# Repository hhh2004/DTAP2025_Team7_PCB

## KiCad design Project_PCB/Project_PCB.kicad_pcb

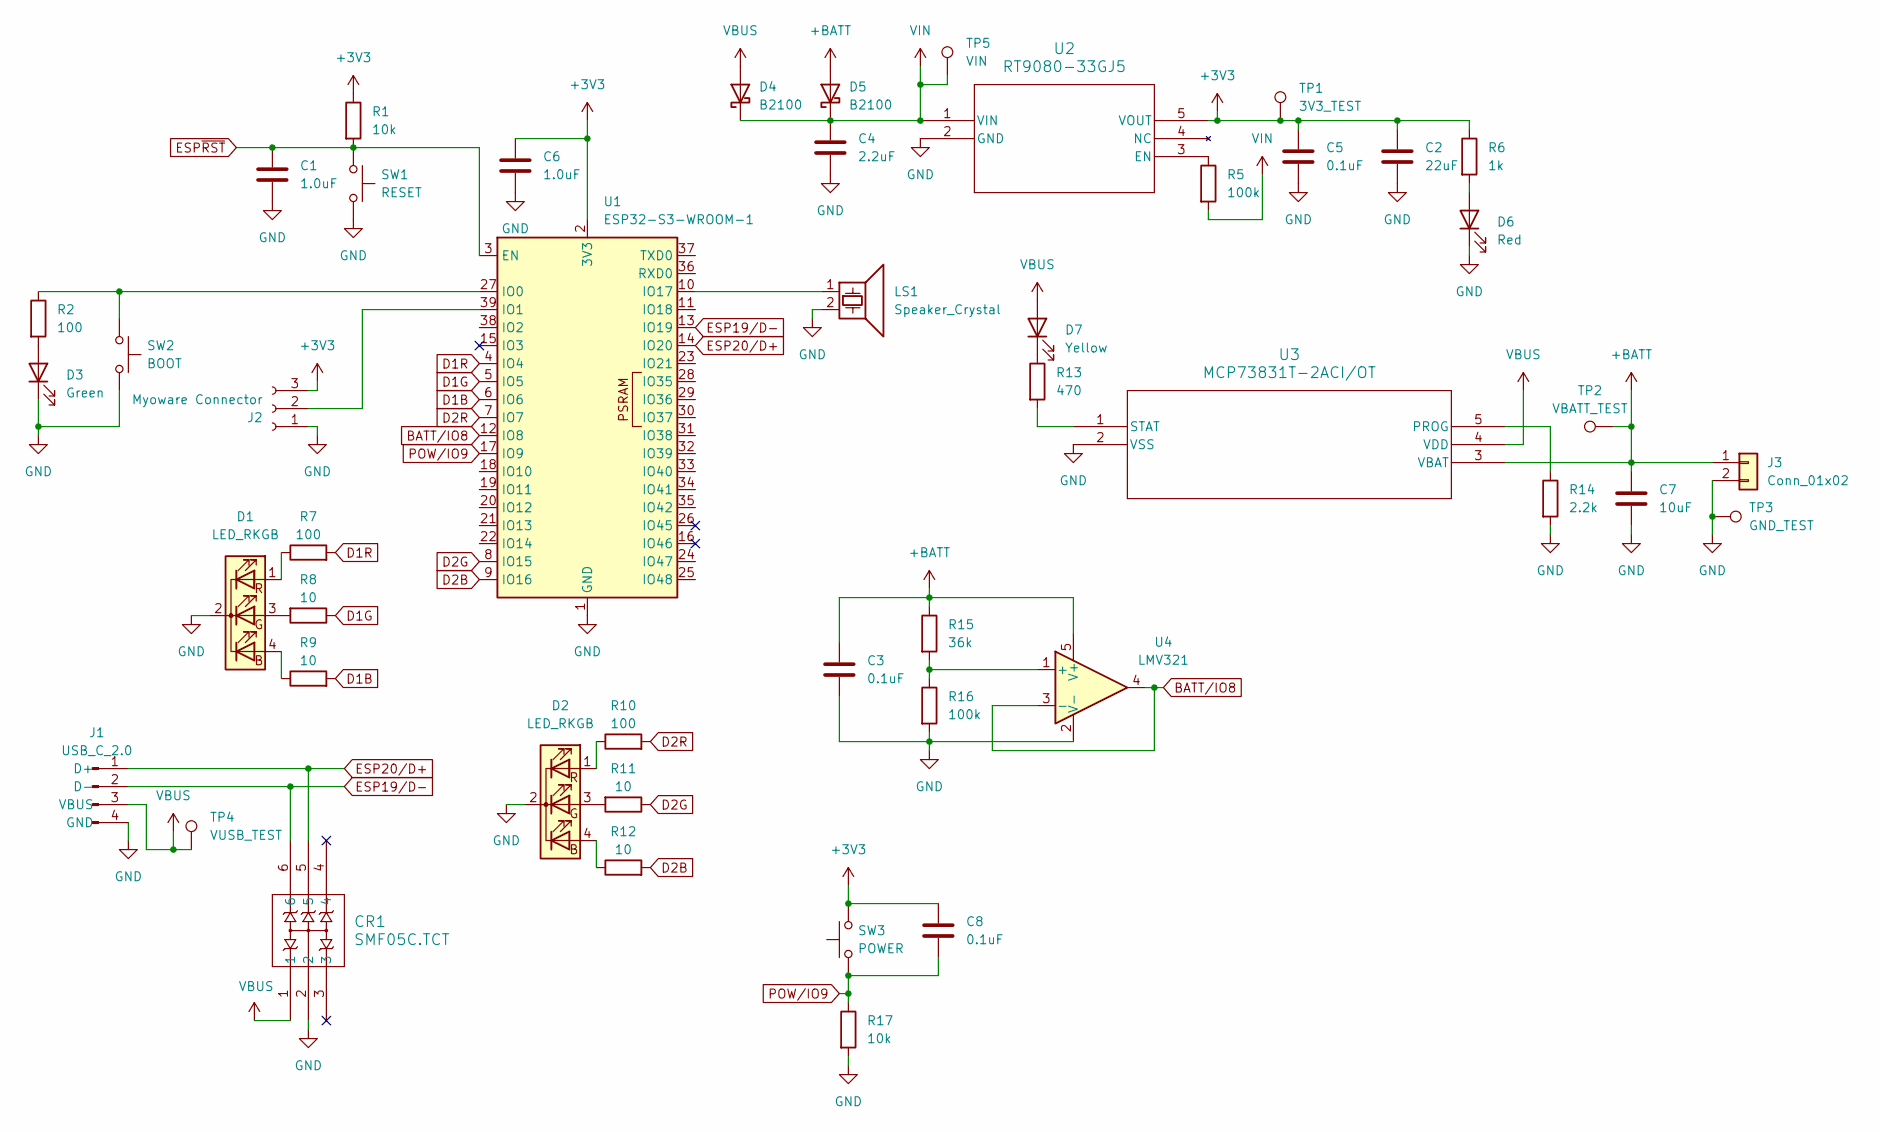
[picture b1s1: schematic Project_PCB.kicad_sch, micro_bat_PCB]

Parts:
C1, C6: 1.0uF; C_0603_1608Metric_Pad1.08x0.95mm_HandSolder
C2: 22uF; C_Radial_D6.3mm_H7.0mm_P2.50mm
C3, C5, C8: 0.1uF; C_0603_1608Metric_Pad1.08x0.95mm_HandSolder
C4: 2.2uF; C_Radial_D5.0mm_H11.0mm_P2.00mm
C7: 10uF; C_Radial_D5.0mm_H11.0mm_P2.00mm
CR1: SMF05C.TCT; SC70-6L_SEM
D1, D2: LED_RKGB; PinHeader_1x04_P2.54mm_Vertical
D3: Green; LED_0805_2012Metric_Pad1.15x1.40mm_HandSolder
D4, D5: B2100; D_SMB_Handsoldering
D6: Red; LED_0805_2012Metric_Pad1.15x1.40mm_HandSolder
D7: Yellow; LED_0805_2012Metric_Pad1.15x1.40mm_HandSolder
J1: USB_C_2.0; PinHeader_1x04_P2.54mm_Vertical
J2: Myoware Connector; PinHeader_1x03_P2.54mm_Vertical
J3: Conn_01x02; JST_PH_S2B-PH-SM4-TB_1x02-1MP_P2.00mm_Horizontal
LS1: Speaker_Crystal; LDBZPN1705
R1, R17: 10k; R_0603_1608Metric_Pad0.98x0.95mm_HandSolder
R2, R7, R10: 100; R_0603_1608Metric_Pad0.98x0.95mm_HandSolder
R5, R16: 100k; R_0603_1608Metric_Pad0.98x0.95mm_HandSolder
R6: 1k; R_0603_1608Metric_Pad0.98x0.95mm_HandSolder
R8, R9, R11, R12: 10; R_0603_1608Metric_Pad0.98x0.95mm_HandSolder
R13: 470; R_0603_1608Metric_Pad0.98x0.95mm_HandSolder
R14: 2.2k; R_0603_1608Metric_Pad0.98x0.95mm_HandSolder
R15: 36k; R_0603_1608Metric_Pad0.98x0.95mm_HandSolder
SW1: RESET; SW_SPST_PTS647_Sx38
SW2: BOOT; SW_Push_1P1T_NO_CK_KSC6xxJ
SW3: POWER; PinHeader_1x02_P2.54mm_Vertical
TP1: 3V3_TEST; TestPoint_THTPad_D2.0mm_Drill1.0mm
TP2: VBATT_TEST; TestPoint_THTPad_D2.0mm_Drill1.0mm
TP3: GND_TEST; TestPoint_THTPad_D2.0mm_Drill1.0mm
TP4: VUSB_TEST; TestPoint_THTPad_D2.0mm_Drill1.0mm
TP5: VIN; TestPoint_THTPad_D2.0mm_Drill1.0mm
U1: ESP32-S3-WROOM-1
U2: RT9080-33GJ5; TSOT-23-5_RIT
U3: MCP73831T-2ACI/OT; SOT-23-5_MC_MCH
U4: LMV321; SOT-353_SC-70-5_Handsoldering

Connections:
+3V3: C2.1, C5.1, C6.1, C8.1, J2.3, R1.1, R6.1, SW3.2, TP1.1, U1.2 (3V3), U2.5 (VOUT)
+BATT: C3.1, C7.1, D5.2 (A), J3.1, R15.1, TP2.1, U3.3 (VBAT), U4.5 (V+)
BATT/IO8: U1.12 (IO8), U4.3 (-), U4.4
D1B: R9.2, U1.6 (IO6)
D1G: R8.1, U1.5 (IO5)
D1R: R7.2, U1.4 (IO4)
D2B: R12.2, U1.9 (IO16)
D2G: R11.1, U1.8 (IO15)
D2R: R10.2, U1.7 (IO7)
ESP19/D-: CR1.6, J1.2 (D-), U1.13 (IO19)
ESP20/D+: CR1.5, J1.1 (D+), U1.14 (IO20)
ESP~RST: C1.1, R1.2, SW1.1, U1.3 (EN)
GND: C1.2, C2.2, C3.2, C4.2, C5.2, C6.2, C7.2, CR1.2, D1.2 (K), D2.2 (K), D3.1 (K), D6.1 (K), J1.4 (GND), J2.1, J3.2, LS1.2, R14.2, R16.2, R17.2, SW1.2, SW2.2, TP3.1, U1.1 (GND), U1.40 (GND), U1.41 (GND), U2.2 (GND), U3.2 (VSS), U4.2 (V-)
unnamed: D1.4 (BA), R9.1
unnamed: D1.3 (GA), R8.2
unnamed: D1.1 (RA), R7.1
unnamed: D2.4 (BA), R12.1
unnamed: D2.3 (GA), R11.2
unnamed: D2.1 (RA), R10.1
unnamed: D3.2 (A), R2.2
unnamed: D6.2 (A), R6.2
unnamed: D7.1 (K), R13.1
unnamed: J2.2, U1.39 (IO1)
unnamed: R2.1, SW2.1, U1.27 (IO0)
unnamed: LS1.1, U1.10 (IO17)
unnamed: R5.1, U2.3 (EN)
unnamed: R14.1, U3.5 (PROG)
unnamed: R13.2, U3.1 (STAT)
unnamed: R15.2, R16.1, U4.1 (+)
POW/IO9: C8.2, R17.1, SW3.1, U1.17 (IO9)
VBUS: CR1.1, D4.2 (A), D7.2 (A), J1.3 (VBUS), TP4.1, U3.4 (VDD)
VIN: C4.1, D4.1 (K), D5.1 (K), R5.2, TP5.1, U2.1 (VIN)

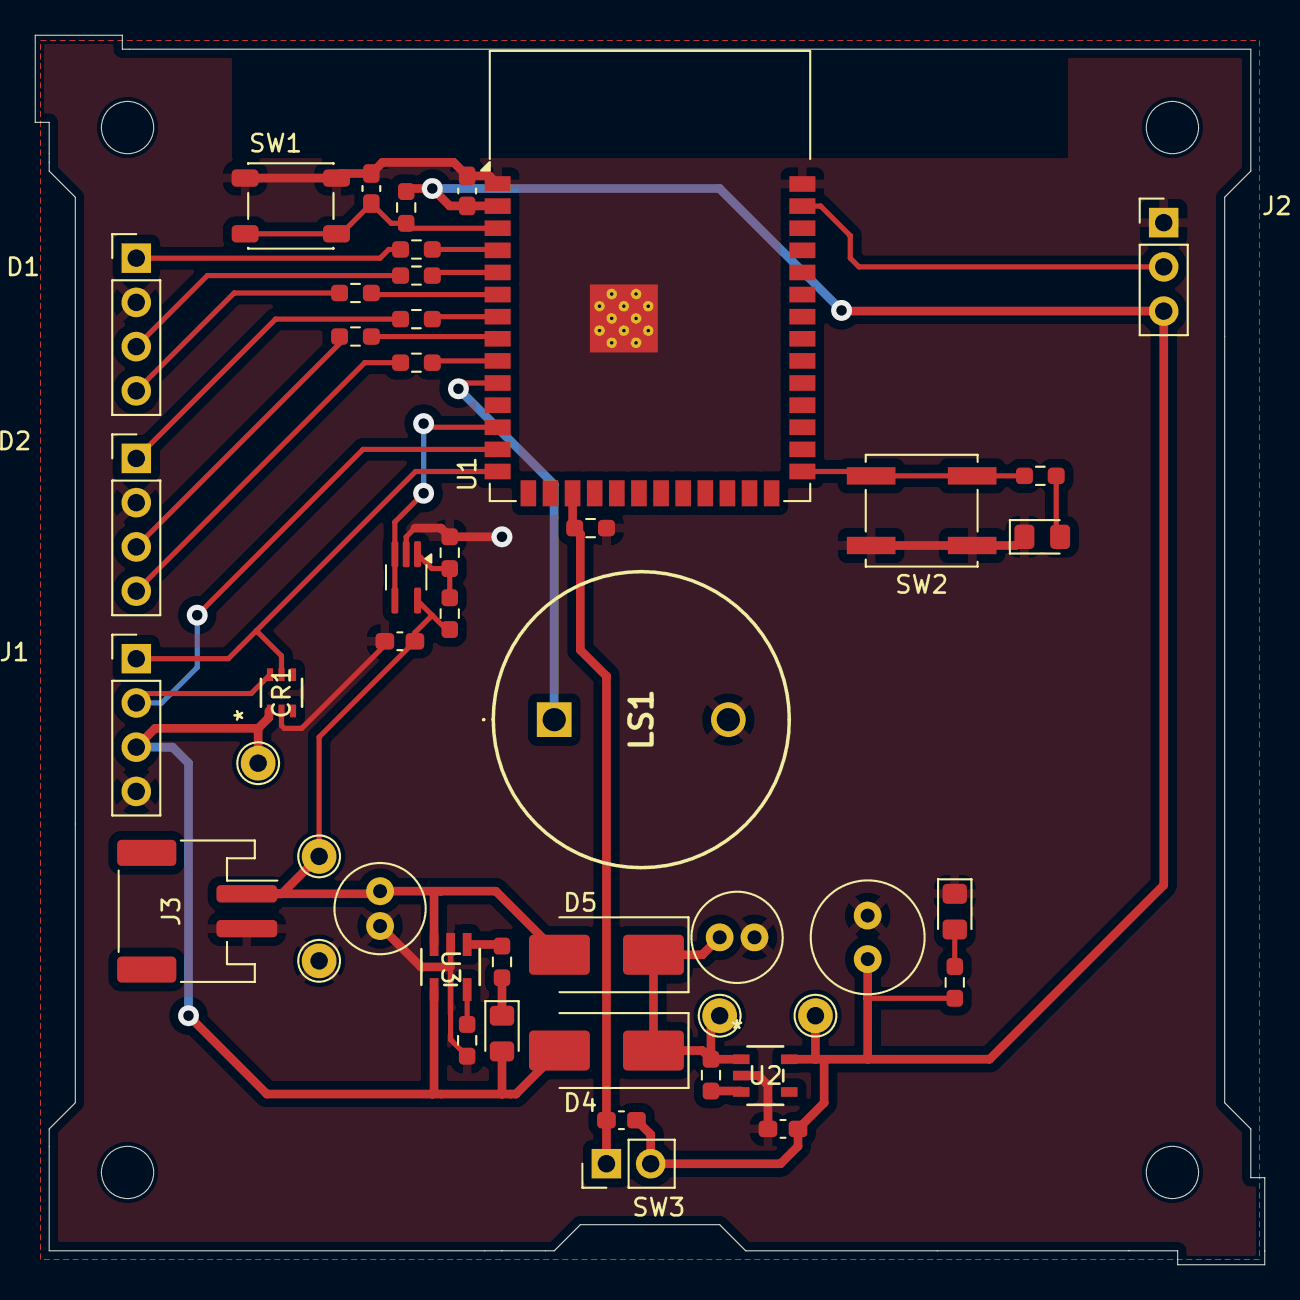
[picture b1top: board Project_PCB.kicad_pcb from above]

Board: 2 copper layers, 70.6 x 70.6 mm, 47 parts (0 on the bottom side), 32 nets.

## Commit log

2025-04-16 Created new project and added some of the components to the schematic
2025-04-16 how do i github
2025-04-25 Changed mcu to ESP32-S3-WROOM-1 and updated some connections.
2025-05-07 minor updates to schematic
2025-05-07 Most of ESP module finished
2025-05-07 Finished initial version of schematic
2025-05-08 Made recommended changes, added some footprints
2025-05-09 Finalized schematic, assigned all footprints
2025-05-14 Started work on PCB layout, made basic progress
2025-05-15 Made progress on PCB layout; minor changes in schematic to ease routing
2025-05-16 Finished PCB design, added alignment tabs
2025-05-20 Updated PCB layout to fix issues with design
